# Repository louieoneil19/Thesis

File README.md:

# Solar-Powered Buck-Boost Converter — Thesis Project

An STM32-based MPPT buck-boost converter for solar-powered soil moisture monitoring and pump control.

## Overview

This project presents the design and implementation of a solar-powered irrigation system optimised for off-grid rural use. The system integrates a photovoltaic panel, a non-inverting DC–DC buck-boost converter, a backup battery, a water pump, and a microcontroller-based control unit on a custom four-layer printed circuit board. A perturb-and-observe maximum power point tracking (MPPT) algorithm is implemented to maximise energy extraction from the solar panel across varying irradiance and temperature conditions. A capacitive soil moisture sensor drives a separate pump-control loop, varying pump speed in discrete stages based on measured soil dryness. The converter was validated in MATLAB Simulink and characterised experimentally through duty-cycle sweeps, with the measured input–output relationships closely matching theoretical predictions. The completed system demonstrates autonomous solar energy harvesting and adaptive water delivery, providing a viable platform for off-grid agricultural applications in resource-limited regions.

## Repository Structure
```
.
├── firmware/          STM32CubeIDE project (STM32F446RE)
│   ├── Core/          Application source code (main.c, peripherals)
│   ├── Drivers/       STM32 HAL drivers
│   └── *.ioc          STM32CubeMX configuration
│
└── hardware/          KiCad PCB design
├── SolarSystem/   KiCad project files (schematic + PCB layout)
├── gerbers/       Manufacturing files for PCB fabrication
├── libraries/     Custom footprints and symbols
├── SolarSystem Layout.pdf   PDF file of SolarSystem schematics
└── SolarSystem_BOM.csv   Bill of materials
```

## Where to Find the Main Code

The primary application logic lives in:

**[`firmware/Core/Src/main.c`](firmware/Core/Src/main.c)**

This file contains all the custom application code, including:

- **MPPT algorithm** — `Run_MPPT()`, `track_mpp_20_seconds()`
- **I-V curve sweep** — `Run_IV_Sweep()`
- **Sensor reading** — `Read_Panel_Sensors()`, `Process_ADC_Buffer()`
- **Soil moisture control** — `Run_Soil_Moisture_Control()`, `find_moisture_calibration()`
- **Pump control** — `Set_Converter_Duty()`, `Set_Manual_Duties()`
- **Calibration routines** — `find_calibration_values()`
- **Telemetry output** — `Print_Panel_Sensors()`

The other files in `firmware/Core/Src/` (such as `stm32f4xx_hal_msp.c`, `stm32f4xx_it.c`, `syscalls.c`, `sysmem.c`, and `system_stm32f4xx.c`) are auto-generated by STM32CubeMX and contain HAL initialisation and system-level boilerplate — they generally don't need to be modified.

## Hardware

- **MCU:** STM32F446RE (ARM Cortex-M4 @ 180 MHz)
- **Topology:** Synchronous buck-boost converter
- **Sensing:** Panel voltage/current (ADC), soil moisture probe
- **Control:** PWM duty-cycle modulation for MPPT
- **Output:** Pump driver with variable speed (PUMP_OFF/SLOW/FAST/FULL)

## Firmware Features

- MPPT algorithm (perturb and observe)
- I-V curve sweep for panel characterisation
- Soil moisture calibration (dry/wet bounds)
- Automated pump control based on moisture thresholds
- UART telemetry for monitoring and debugging

## Building the Firmware

**Requirements:**
- [STM32CubeIDE](https://www.st.com/en/development-tools/stm32cubeide.html) (tested on v1.x)
- ST-LINK programmer (or compatible STM32 board with built-in debugger)

**Steps:**
1. Open STM32CubeIDE
2. **File → Import → Existing Projects into Workspace**
3. Browse to the `firmware/` folder in this repository
4. Select the project and click **Finish**
5. Build with **Cmd+B** (macOS) or **Ctrl+B** (Windows/Linux)
6. Flash to the target with the green Run arrow

## Viewing the Hardware

The PCB design is created in [KiCad](https://www.kicad.org/) (free, open-source).

**To view the schematic and PCB layout:**
1. Install KiCad (version 7 or newer)
2. Open `hardware/SolarSystem/` and double-click the `.kicad_pro` file

**Manufacturing files:**
The `hardware/gerbers/` folder contains ready-to-fabricate Gerber files compatible with most PCB manufacturers (JLCPCB, PCBWay, OshPark, etc.).

## Author

Louie O'Neil

## License

This project is shared as part of academic thesis work. See `LICENSE` for details.

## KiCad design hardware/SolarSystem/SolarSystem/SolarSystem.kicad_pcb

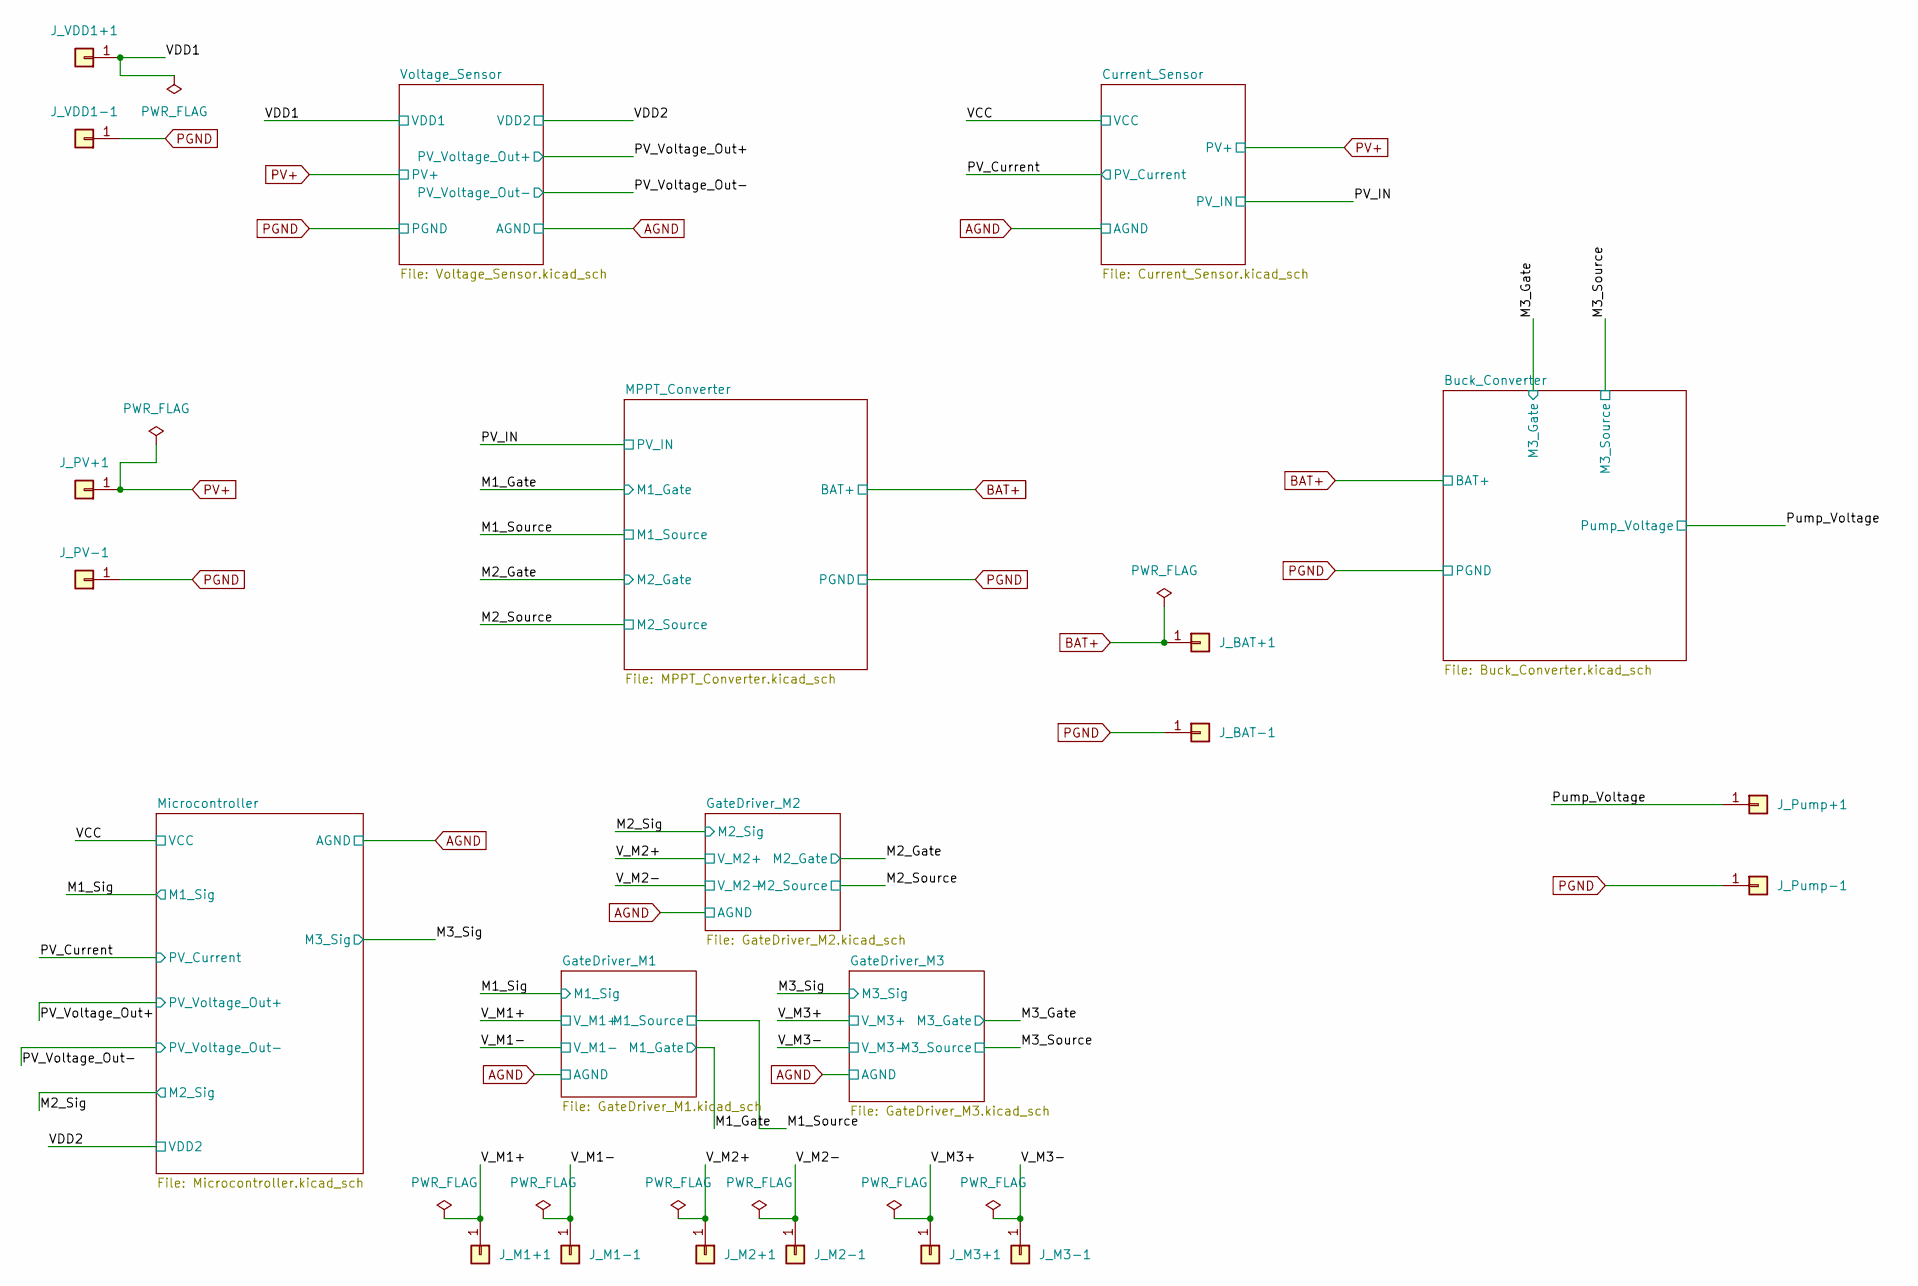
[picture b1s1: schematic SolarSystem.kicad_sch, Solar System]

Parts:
J_BAT+1: Conn_01x01; Banana_Jack_1Pin
J_BAT-1: Conn_01x01; Banana_Jack_1Pin
J_M1+1, J_M1-1, J_M2+1, J_M2-1, J_M3+1, J_M3-1: Conn_01x01; Banana_Jack_1Pin
J_PV+1: Conn_01x01; Banana_Jack_1Pin
J_PV-1: Conn_01x01; Banana_Jack_1Pin
J_Pump+1: Conn_01x01; Banana_Jack_1Pin
J_Pump-1: Conn_01x01; Banana_Jack_1Pin
J_VDD1+1, J_VDD1-1: Conn_01x01; Banana_Jack_1Pin

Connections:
/M1_Source: J_M1-1.1; also elsewhere on the board
/M3_Source: J_M3-1.1; also elsewhere on the board
/Pump_Voltage: J_Pump+1.1; also elsewhere on the board
/VDD1: J_VDD1+1.1; also elsewhere on the board
/V_M1+: J_M1+1.1; also elsewhere on the board
/V_M2+: J_M2+1.1; also elsewhere on the board
/V_M3+: J_M3+1.1; also elsewhere on the board
BAT+: J_BAT+1.1; also elsewhere on the board
PGND: J_BAT-1.1, J_M2-1.1, J_PV-1.1, J_Pump-1.1, J_VDD1-1.1; also elsewhere on the board
PV+: J_PV+1.1; also elsewhere on the board

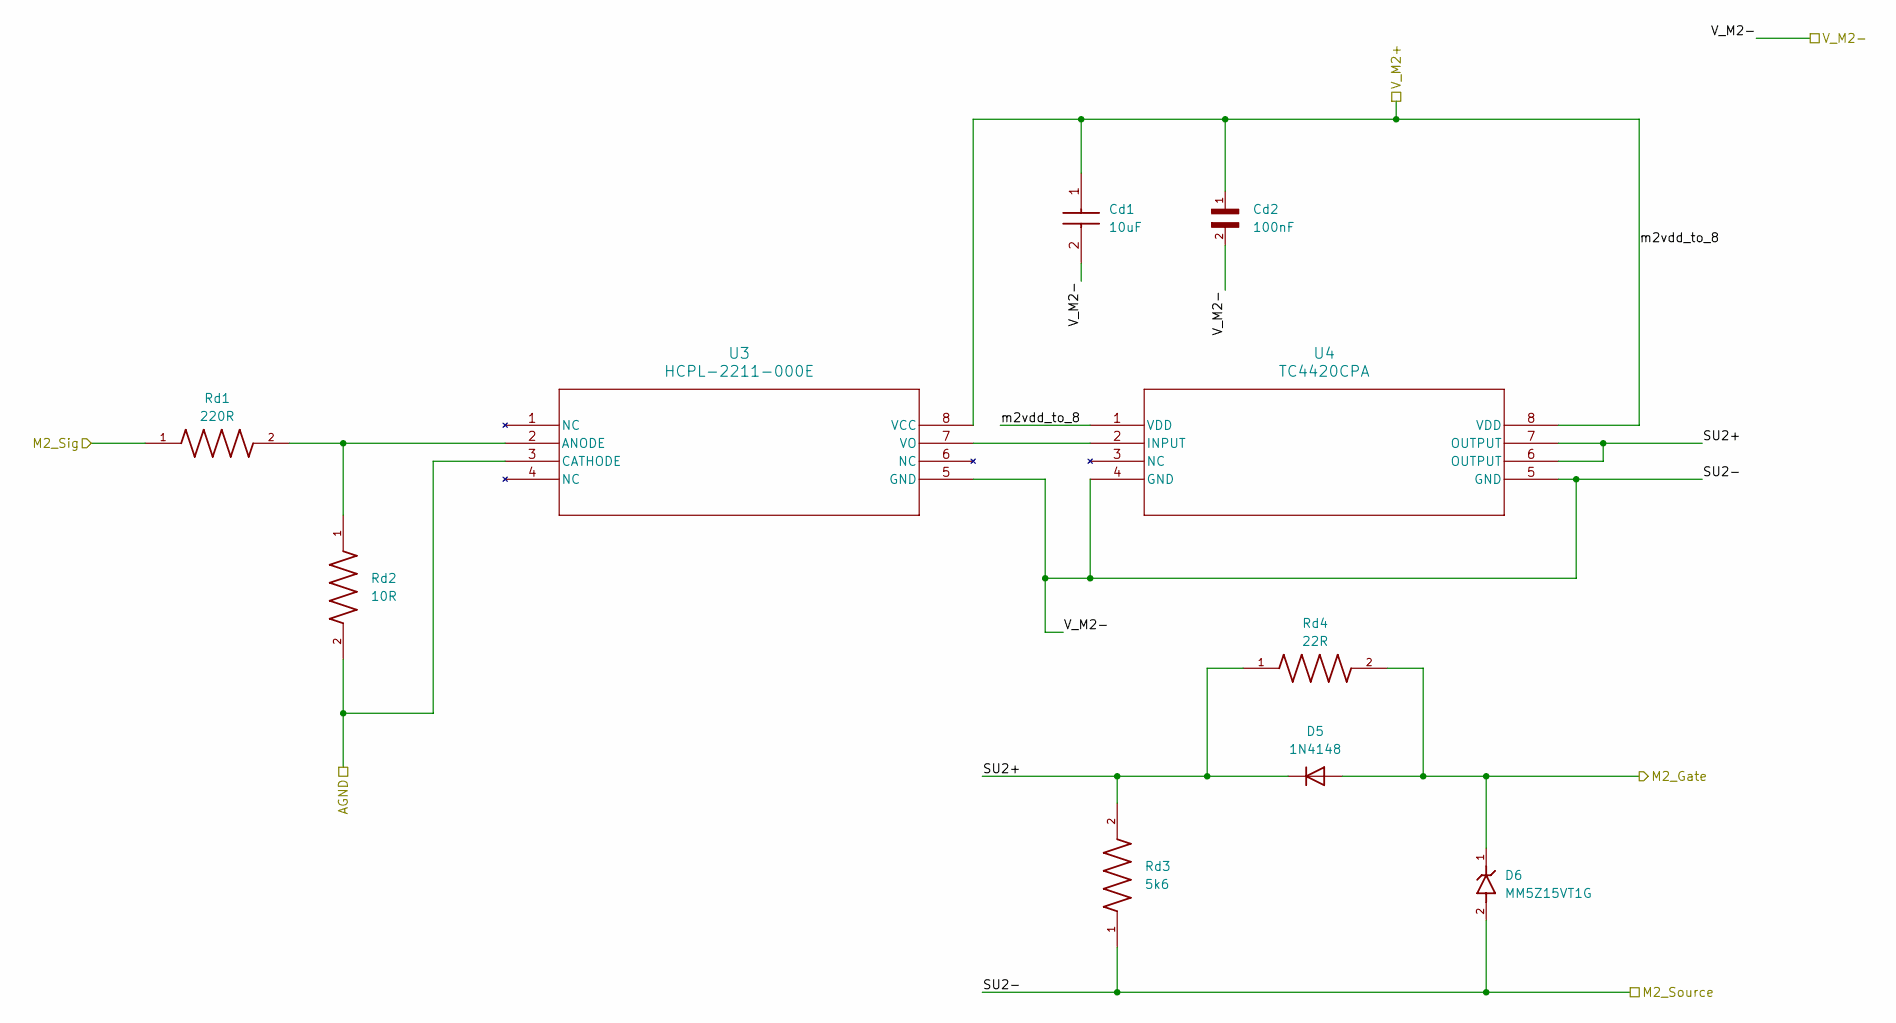
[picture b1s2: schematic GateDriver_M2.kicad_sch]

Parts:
Cd1: 10uF; CAPC3225X280N; Manufacturer_Part_Number AGC1210X7R500-106KNE
Cd2: 100nF; CAPC0603X33N
D5: 1N4148; D_DO-35_SOD27_P7.62mm_Horizontal
D6: MM5Z15VT1G; SODFL1608X70N; PARTREV 17
Rd1: 220R; RESC2012X60N
Rd2: 10R; RESC2012X60N
Rd3: 5k6; RESC2012X50N
Rd4: 22R; RESC2012X60N
U3: HCPL-2211-000E; SO-8_AVA
U4: TC4420CPA; PDIP8_300MC_MCH

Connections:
/GateDriver_M2/SU2+: D5.1 (K), Rd3.2, Rd4.1, U4.6 (OUTPUT), U4.7 (OUTPUT)
/M2_Gate: D5.2 (A), D6.1, Rd4.2; also elsewhere on the board
/M2_Sig: Rd1.1; also elsewhere on the board
/V_M2+: Cd1.1, Cd2.1, U3.8 (VCC), U4.1 (VDD), U4.8 (VDD); also elsewhere on the board
AGND: Rd2.2, U3.3 (CATHODE); also elsewhere on the board
unnamed: Rd1.2, Rd2.1, U3.2 (ANODE)
unnamed: U3.7 (VO), U4.2 (INPUT)
PGND: Cd1.2, Cd2.2, D6.2, Rd3.1, U3.5 (GND), U4.4 (GND), U4.5 (GND); also elsewhere on the board

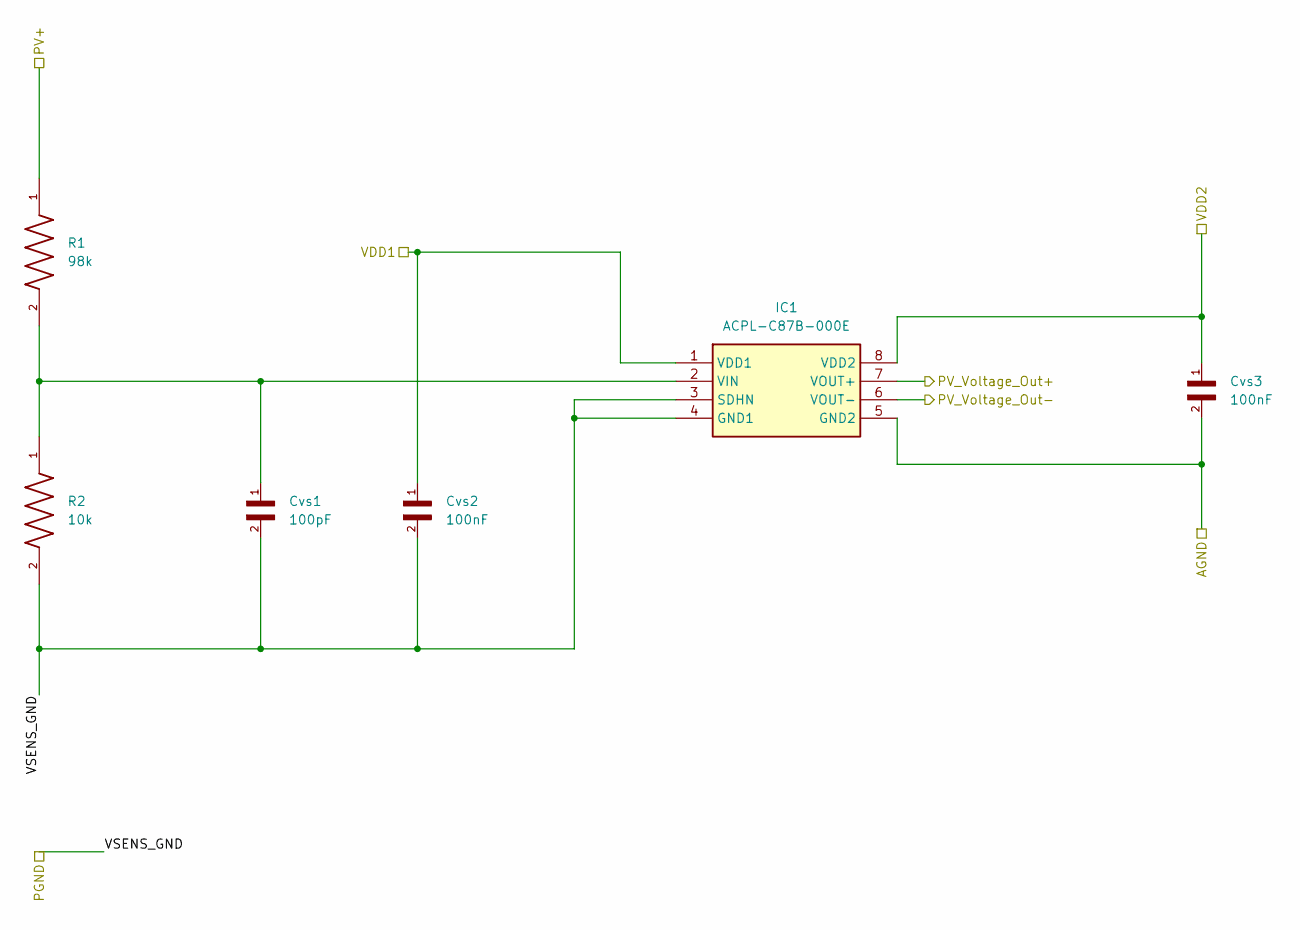
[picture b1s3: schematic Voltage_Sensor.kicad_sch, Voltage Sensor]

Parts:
Cvs1: 100pF; CAPC0603X33N
Cvs2, Cvs3: 100nF; CAPC0603X33N
IC1: ACPL-C87B-000E; SOIC127P1150X360-8N; Mouser Part Number 630-ACPL-C87B-000E
R1: 98k; RESC2012X60N
R2: 10k; RESC2012X60N

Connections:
/PV_Voltage_Out+: IC1.7 (VOUT+); also elsewhere on the board
/PV_Voltage_Out-: IC1.6 (VOUT-); also elsewhere on the board
/VCC: Cvs3.1, IC1.8 (VDD2); also elsewhere on the board
/VDD1: Cvs2.1, IC1.1 (VDD1); also elsewhere on the board
AGND: Cvs3.2, IC1.5 (GND2); also elsewhere on the board
unnamed: Cvs1.1, IC1.2 (VIN), R1.2, R2.1
PGND: Cvs1.2, Cvs2.2, IC1.3 (SDHN), IC1.4 (GND1), R2.2; also elsewhere on the board
PV+: R1.1; also elsewhere on the board

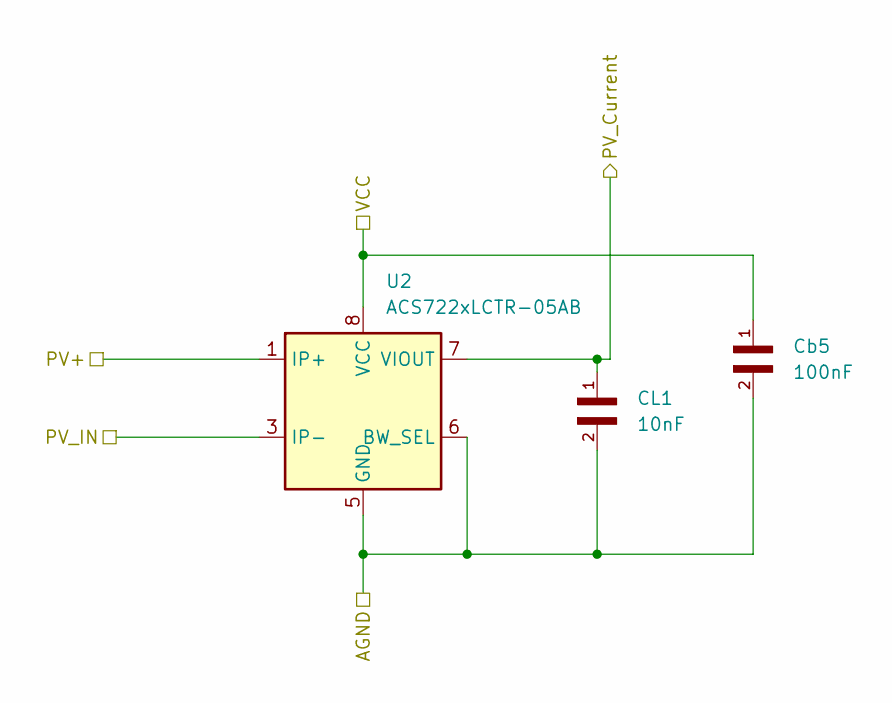
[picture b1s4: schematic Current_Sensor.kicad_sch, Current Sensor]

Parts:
CL1: 10nF; CAPC1005X55N
Cb5: 100nF; CAPC0603X33N
U2: ACS722xLCTR-05AB; SOIC-8_3.9x4.9mm_P1.27mm

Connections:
/PV_Current: CL1.1, U2.7 (VIOUT); also elsewhere on the board
/PV_IN: U2.3 (IP-), U2.4 (IP-); also elsewhere on the board
/VCC: Cb5.1, U2.8 (VCC); also elsewhere on the board
AGND: CL1.2, Cb5.2, U2.5 (GND), U2.6 (BW_SEL); also elsewhere on the board
PV+: U2.1 (IP+), U2.2 (IP+); also elsewhere on the board

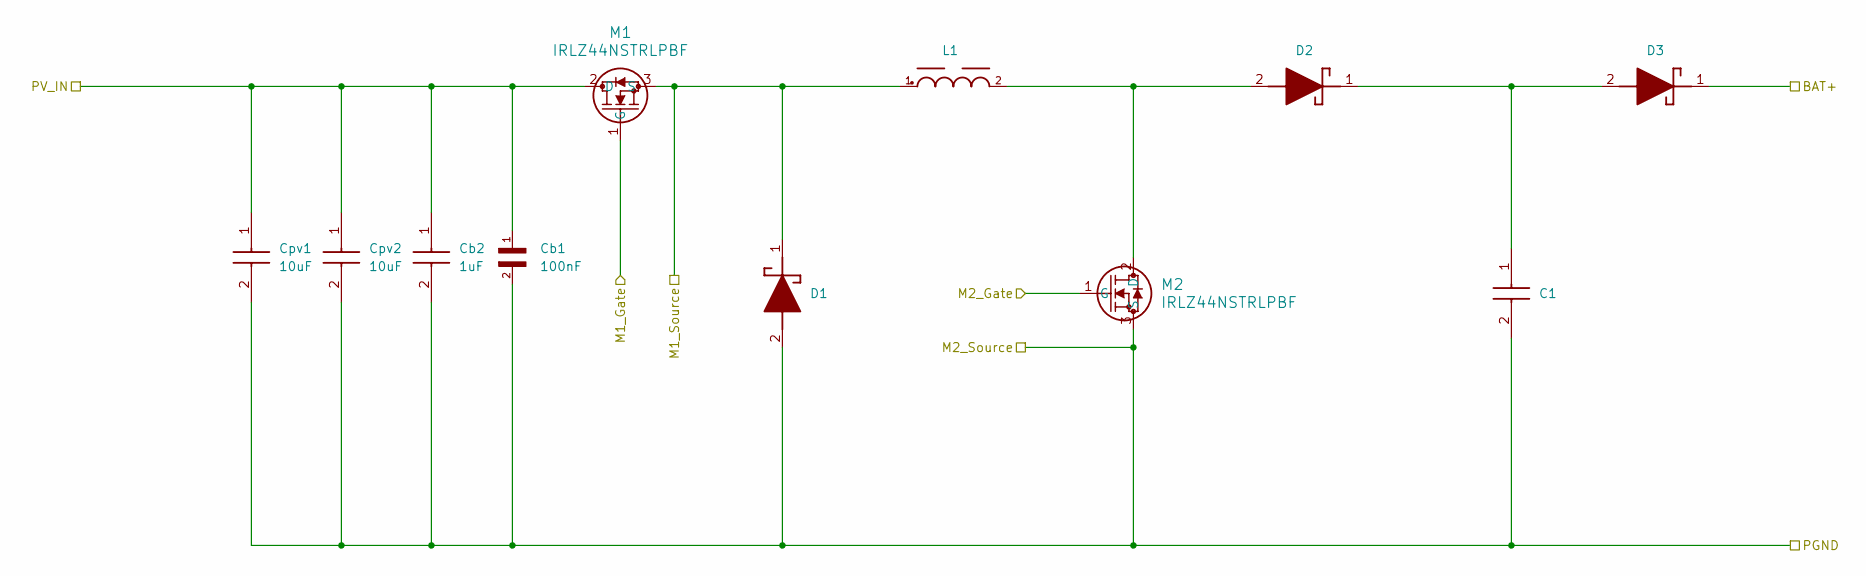
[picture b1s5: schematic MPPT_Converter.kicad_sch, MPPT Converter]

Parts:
C1: ATB107M035; CAPAE660X800N; Manufacturer_Part_Number ATB107M035; Mouser Part Number 598-ATB107M035
Cb1: 100nF; CAPC0603X33N
Cb2: 1uF; CAPC1608X95N; Manufacturer_Part_Number AGC0603X7R250-105KXP
Cpv1, Cpv2: 10uF; CAPC3225X280N; Manufacturer_Part_Number AGC1210X7R500-106KNE
D1, D2, D3: SK34SMA-3G; DIOM5027X240N; Manufacturer_Part_Number SK34SMA-3G; Mouser Part Number 637-SK34SMA-3G
L1: WE-HCF_2920_ROUND; DigiKey_Part_Number 732-11720-ND
M1, M2: IRLZ44NSTRLPBF; NMOSGDS_D2PAK_INF

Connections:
/M1_Gate: M1.1 (G); also elsewhere on the board
/M1_Source: D1.1 (K), L1.1, M1.3 (S); also elsewhere on the board
/M2_Gate: M2.1 (G); also elsewhere on the board
/PV_IN: Cb1.1, Cb2.1, Cpv1.1, Cpv2.1, M1.2 (D); also elsewhere on the board
BAT+: D3.1 (K); also elsewhere on the board
unnamed: C1.1 (+), D2.1 (K), D3.2 (A)
unnamed: D2.2 (A), L1.2, M2.2 (D)
PGND: C1.2 (-), Cb1.2, Cb2.2, Cpv1.2, Cpv2.2, D1.2 (A), M2.3 (S); also elsewhere on the board

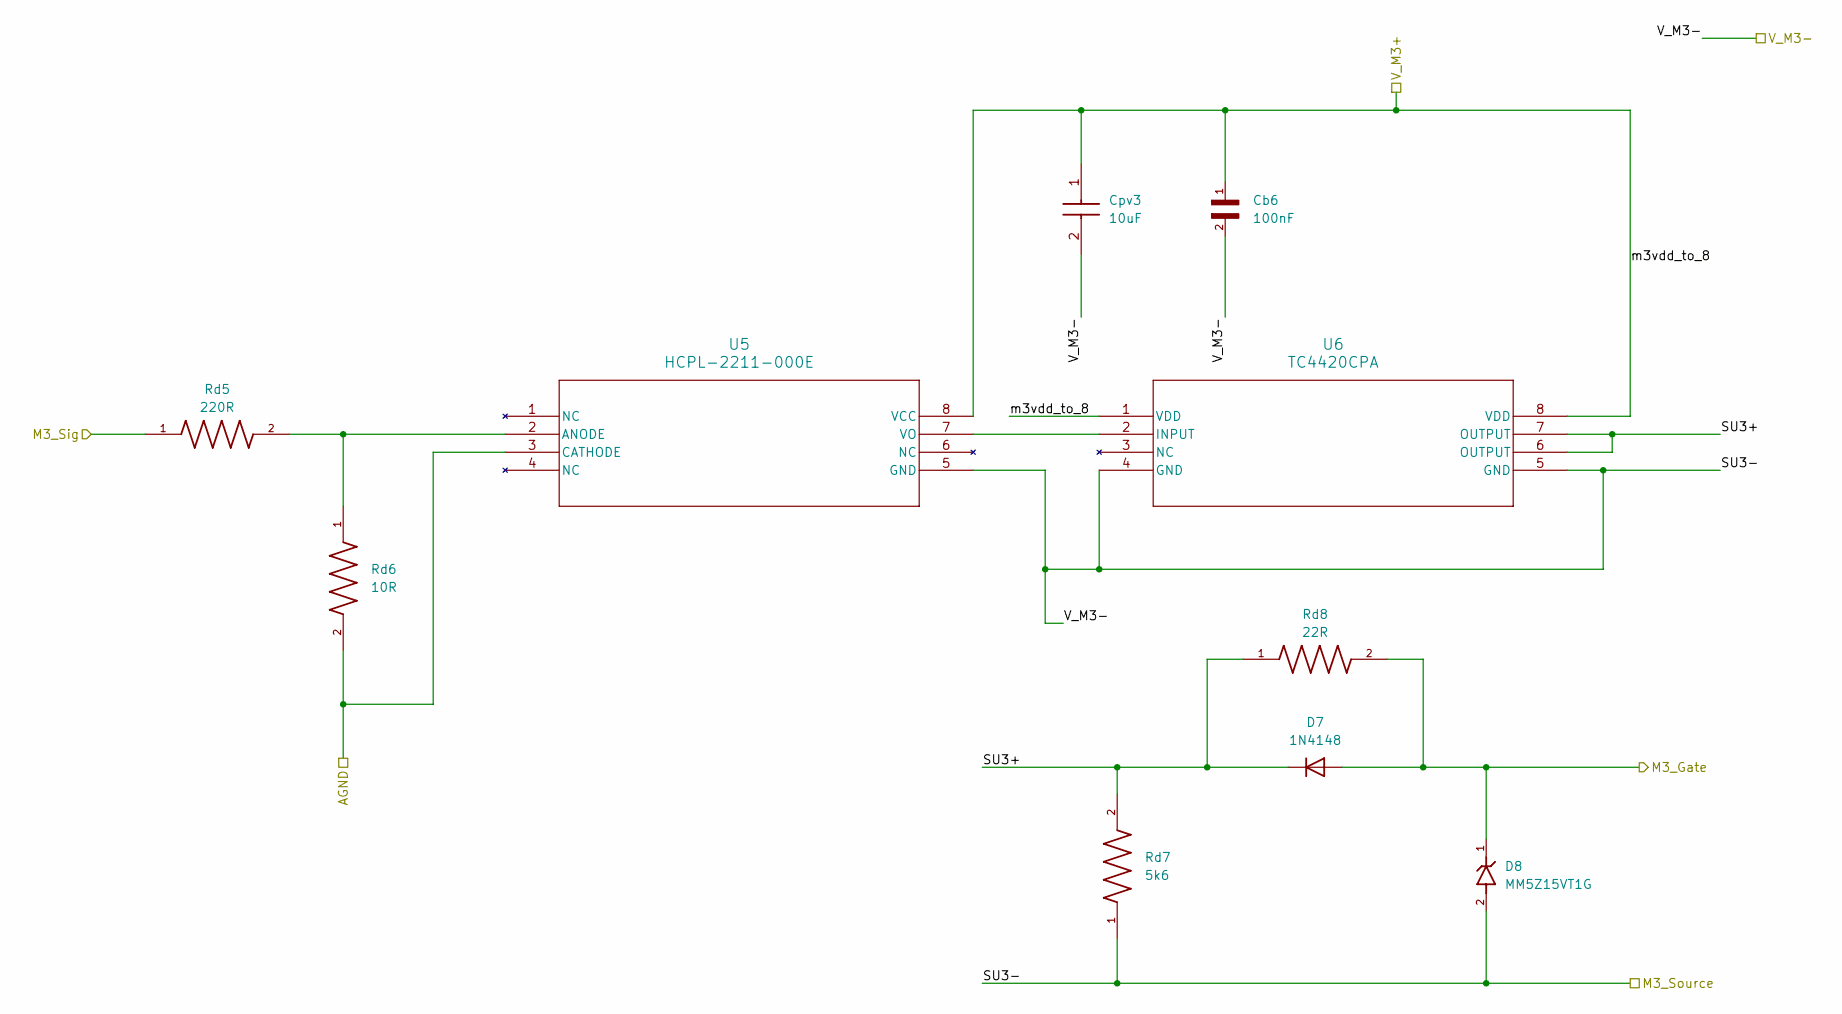
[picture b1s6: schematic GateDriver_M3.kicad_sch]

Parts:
Cb6: 100nF; CAPC0603X33N
Cpv3: 10uF; CAPC3225X280N; Manufacturer_Part_Number AGC1210X7R500-106KNE
D7: 1N4148; D_DO-35_SOD27_P7.62mm_Horizontal
D8: MM5Z15VT1G; SODFL1608X70N; PARTREV 17
Rd5: 220R; RESC2012X60N
Rd6: 10R; RESC2012X60N
Rd7: 5k6; RESC2012X50N
Rd8: 22R; RESC2012X60N
U5: HCPL-2211-000E; SO-8_AVA
U6: TC4420CPA; PDIP8_300MC_MCH

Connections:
/GateDriver_M3/SU3+: D7.1 (K), Rd7.2, Rd8.1, U6.6 (OUTPUT), U6.7 (OUTPUT)
/M3_Gate: D7.2 (A), D8.1, Rd8.2; also elsewhere on the board
/M3_Sig: Rd5.1; also elsewhere on the board
/M3_Source: Cb6.2, Cpv3.2, D8.2, Rd7.1, U5.5 (GND), U6.4 (GND), U6.5 (GND); also elsewhere on the board
/V_M3+: Cb6.1, Cpv3.1, U5.8 (VCC), U6.1 (VDD), U6.8 (VDD); also elsewhere on the board
AGND: Rd6.2, U5.3 (CATHODE); also elsewhere on the board
unnamed: Rd5.2, Rd6.1, U5.2 (ANODE)
unnamed: U5.7 (VO), U6.2 (INPUT)

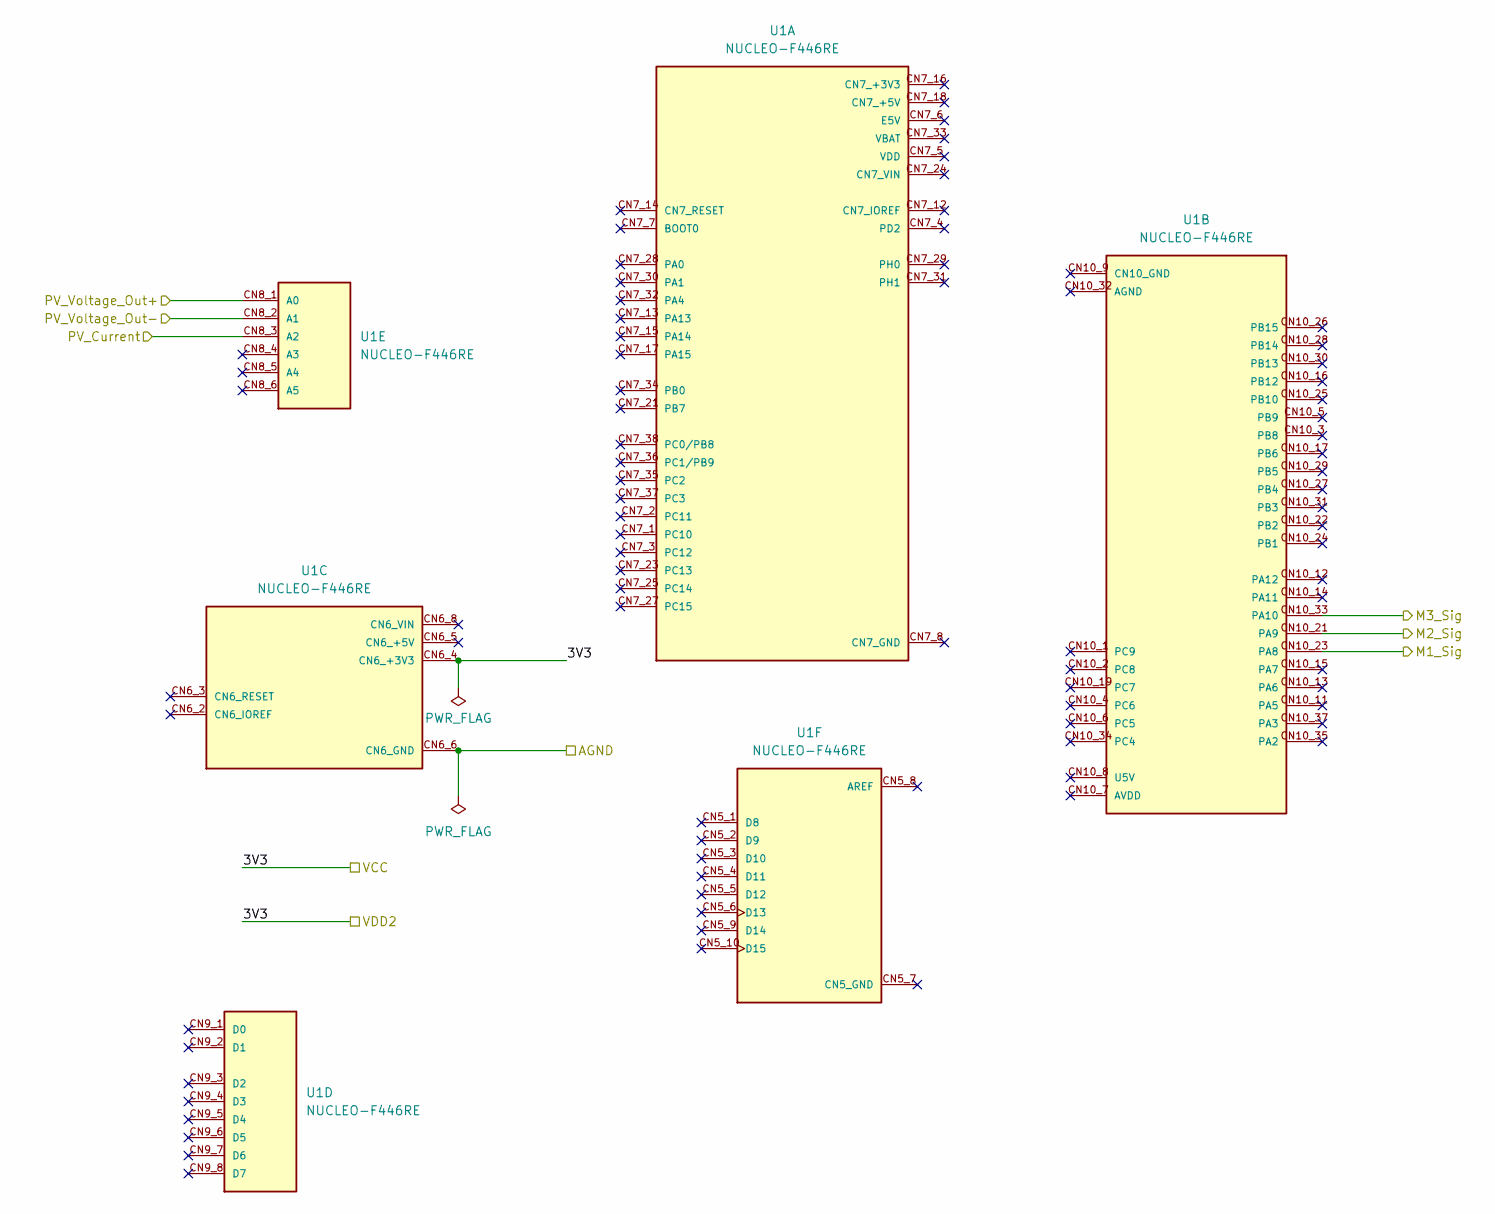
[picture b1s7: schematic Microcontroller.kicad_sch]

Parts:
U1: NUCLEO-F446RE; MODULE_NUCLEO-F446RE; PARTREV 13

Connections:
/M1_Sig: U1.CN10_23 (PA8); also elsewhere on the board
/M2_Sig: U1.CN10_21 (PA9); also elsewhere on the board
/M3_Sig: U1.CN10_33 (PA10); also elsewhere on the board
/PV_Current: U1.CN8_3 (A2); also elsewhere on the board
/PV_Voltage_Out+: U1.CN8_1 (A0); also elsewhere on the board
/PV_Voltage_Out-: U1.CN8_2 (A1); also elsewhere on the board
/VCC: U1.CN6_4 (CN6_+3V3); also elsewhere on the board
AGND: U1.CN6_6 (CN6_GND), U1.CN6_7 (CN6_GND); also elsewhere on the board

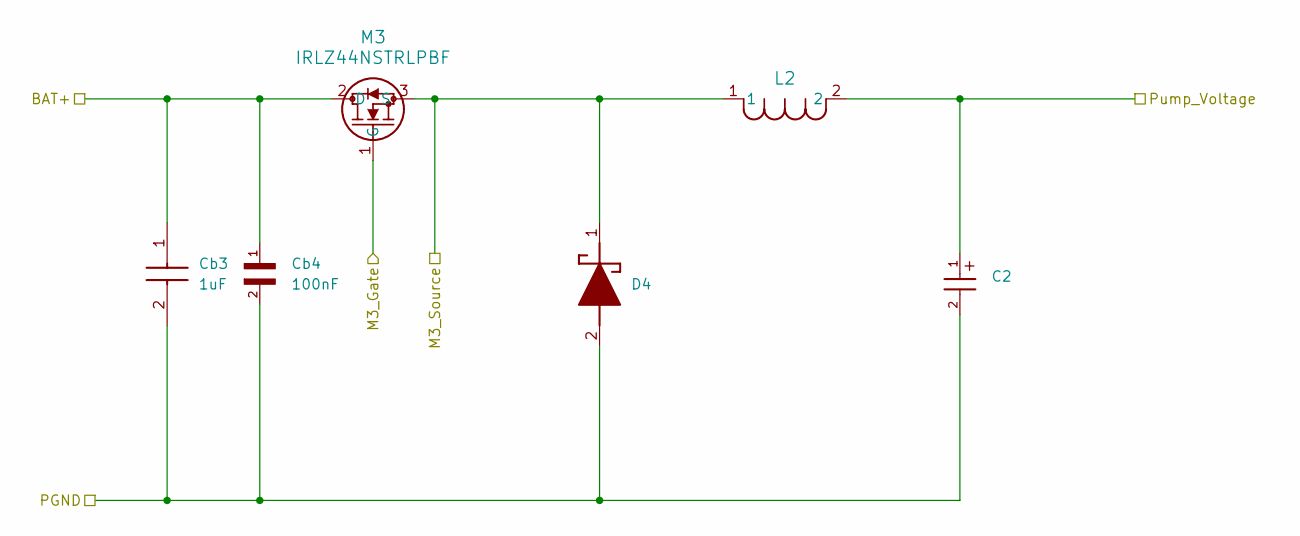
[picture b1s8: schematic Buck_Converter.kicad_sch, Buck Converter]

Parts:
C2: WCAP-ASLI_4X5.5; WCAP-ASLI_4X5.5_DXL_
Cb3: 1uF; CAPC1608X95N; Manufacturer_Part_Number AGC0603X7R250-105KXP
Cb4: 100nF; CAPC0603X33N
D4: SK34SMA-3G; DIOM5027X240N; Manufacturer_Part_Number SK34SMA-3G; Mouser Part Number 637-SK34SMA-3G
L2: SRR1210-471M; IND_BOURNS_SRR1210
M3: IRLZ44NSTRLPBF; NMOSGDS_D2PAK_INF

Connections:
/M3_Gate: M3.1 (G); also elsewhere on the board
/M3_Source: D4.1 (K), L2.1, M3.3 (S); also elsewhere on the board
/Pump_Voltage: C2.1, L2.2; also elsewhere on the board
BAT+: Cb3.1, Cb4.1, M3.2 (D); also elsewhere on the board
PGND: C2.2, Cb3.2, Cb4.2, D4.2 (A); also elsewhere on the board

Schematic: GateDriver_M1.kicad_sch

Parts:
Cd3: 10uF; CAPC3225X280N; Manufacturer_Part_Number AGC1210X7R500-106KNE
Cd4: 100nF; CAPC0603X33N
D9: 1N4148; D_DO-35_SOD27_P7.62mm_Horizontal
D10: MM5Z15VT1G; SODFL1608X70N; PARTREV 17
Rd9: 220R; RESC2012X60N
Rd10: 10R; RESC2012X60N
Rd11: 5k6; RESC2012X50N
Rd12: 22R; RESC2012X60N
U7: HCPL-2211-000E; SO-8_AVA
U8: TC4420CPA; PDIP8_300MC_MCH

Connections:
/GateDriver_M1/SU1+: D9.1 (K), Rd11.2, Rd12.1, U8.6 (OUTPUT), U8.7 (OUTPUT)
/M1_Gate: D9.2 (A), D10.1, Rd12.2; also elsewhere on the board
/M1_Sig: Rd9.1; also elsewhere on the board
/M1_Source: Cd3.2, Cd4.2, D10.2, Rd11.1, U7.5 (GND), U8.4 (GND), U8.5 (GND); also elsewhere on the board
/V_M1+: Cd3.1, Cd4.1, U7.8 (VCC), U8.1 (VDD), U8.8 (VDD); also elsewhere on the board
AGND: Rd10.2, U7.3 (CATHODE); also elsewhere on the board
unnamed: Rd9.2, Rd10.1, U7.2 (ANODE)
unnamed: U7.7 (VO), U8.2 (INPUT)

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
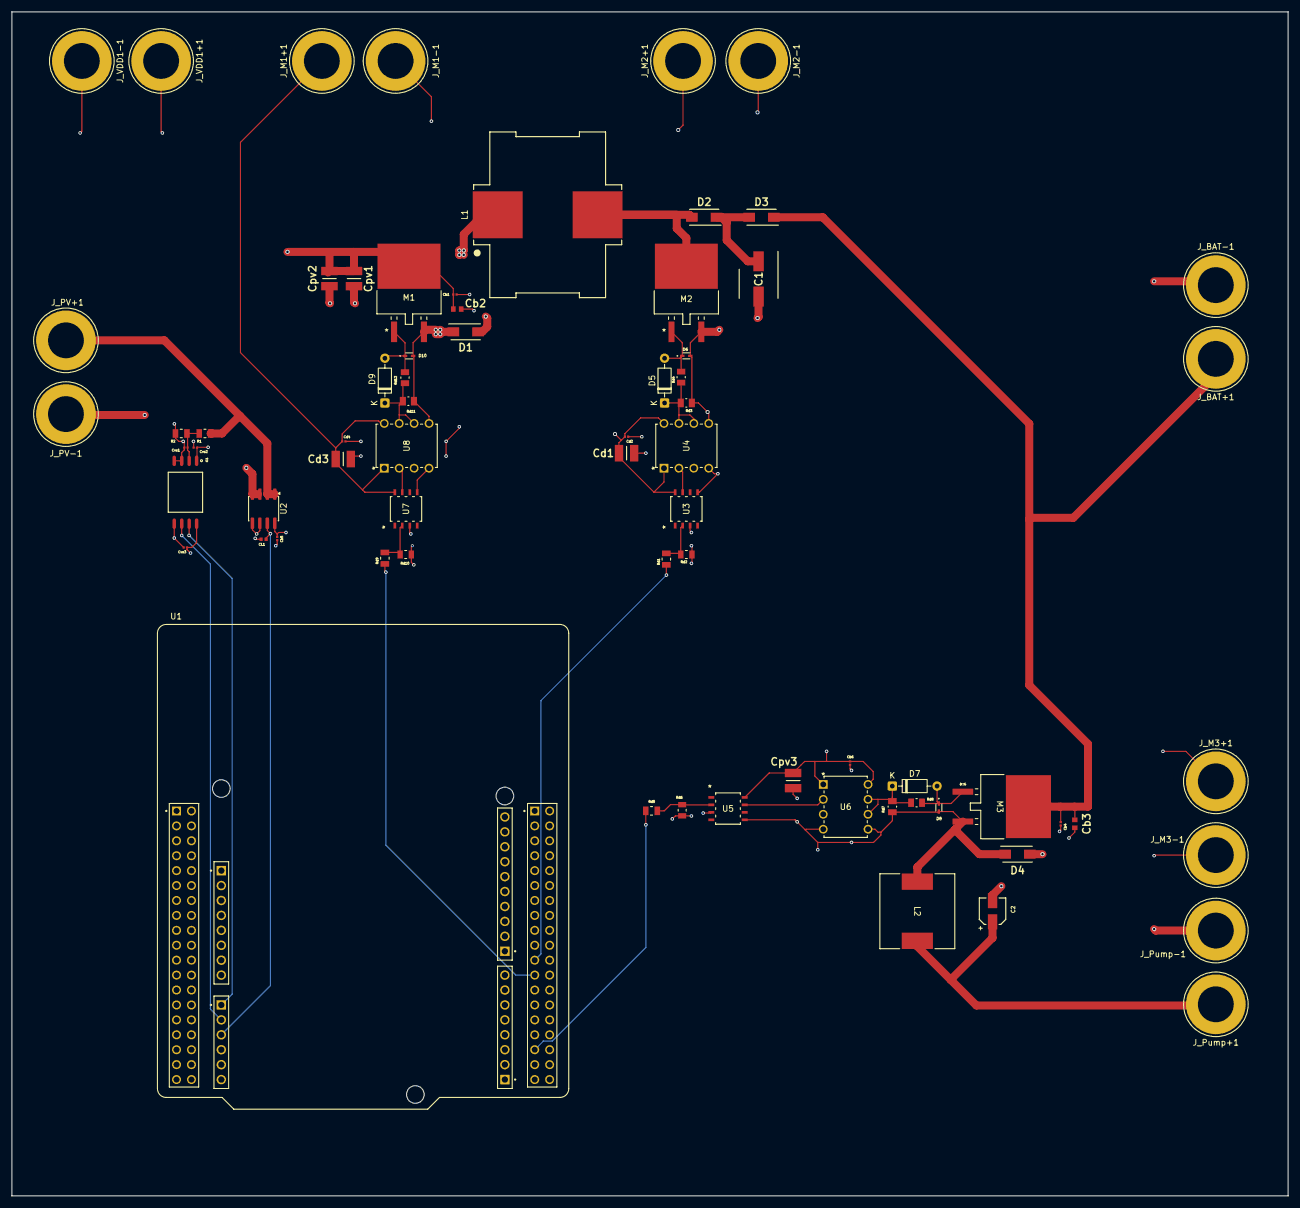
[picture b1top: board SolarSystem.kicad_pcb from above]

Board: 4 copper layers, 217.2 x 201.5 mm, 71 parts (0 on the bottom side), 34 nets.

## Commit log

2026-05-23 Reorganise into firmware/ and hardware/ subfolders
2026-05-23 Remove reorganisation script
2026-05-23 Revise README for solar-powered irrigation project
    Updated the README to reflect the solar-powered buck-boost converter project details, including an overview, repository structure, hardware specifications, firmware features, and instructions for bui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
2026-05-23 Update README
    Added section detailing where to find the main application code and its functionalities.
